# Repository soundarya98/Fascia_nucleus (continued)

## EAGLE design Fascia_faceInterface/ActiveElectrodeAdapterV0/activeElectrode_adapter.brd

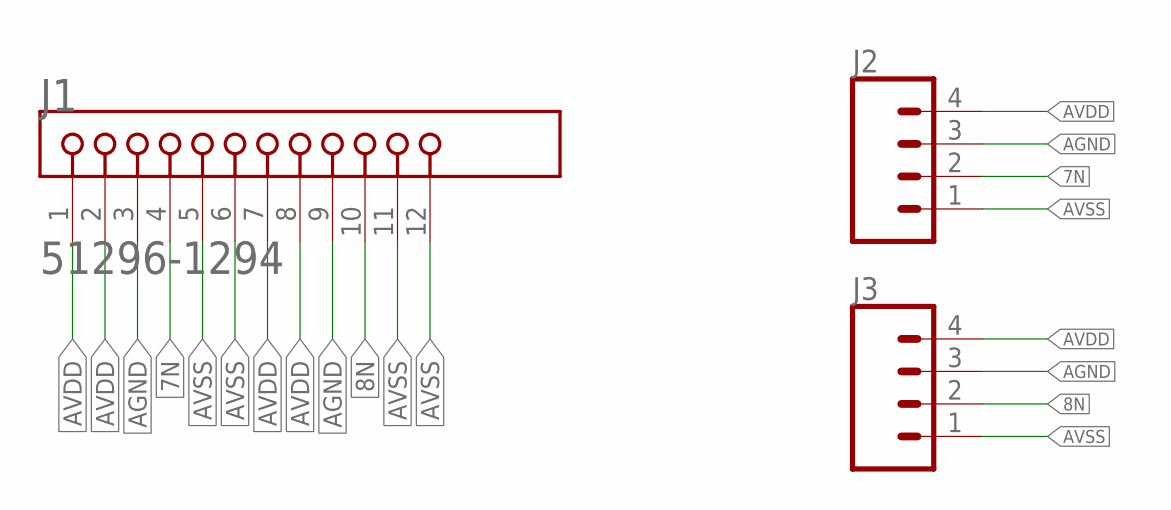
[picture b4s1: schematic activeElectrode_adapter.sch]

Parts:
J1: MOLEX_51296-1294_FLEX
J2, J3: CONN_04AE_4PIN; AE-4-PTH

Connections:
7N: J1.4, J2.2
8N: J1.10, J3.2
AGND: J1.3, J1.9, J2.3, J3.3
AVDD: J1.1, J1.2, J1.7, J1.8, J2.4, J3.4
AVSS: J1.5, J1.6, J1.11, J1.12, J2.1, J3.1

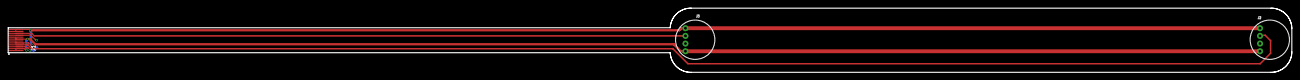
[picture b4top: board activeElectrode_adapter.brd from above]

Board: 2 copper layers, 334.2 x 16.7 mm, 3 parts (0 on the bottom side), 5 nets.

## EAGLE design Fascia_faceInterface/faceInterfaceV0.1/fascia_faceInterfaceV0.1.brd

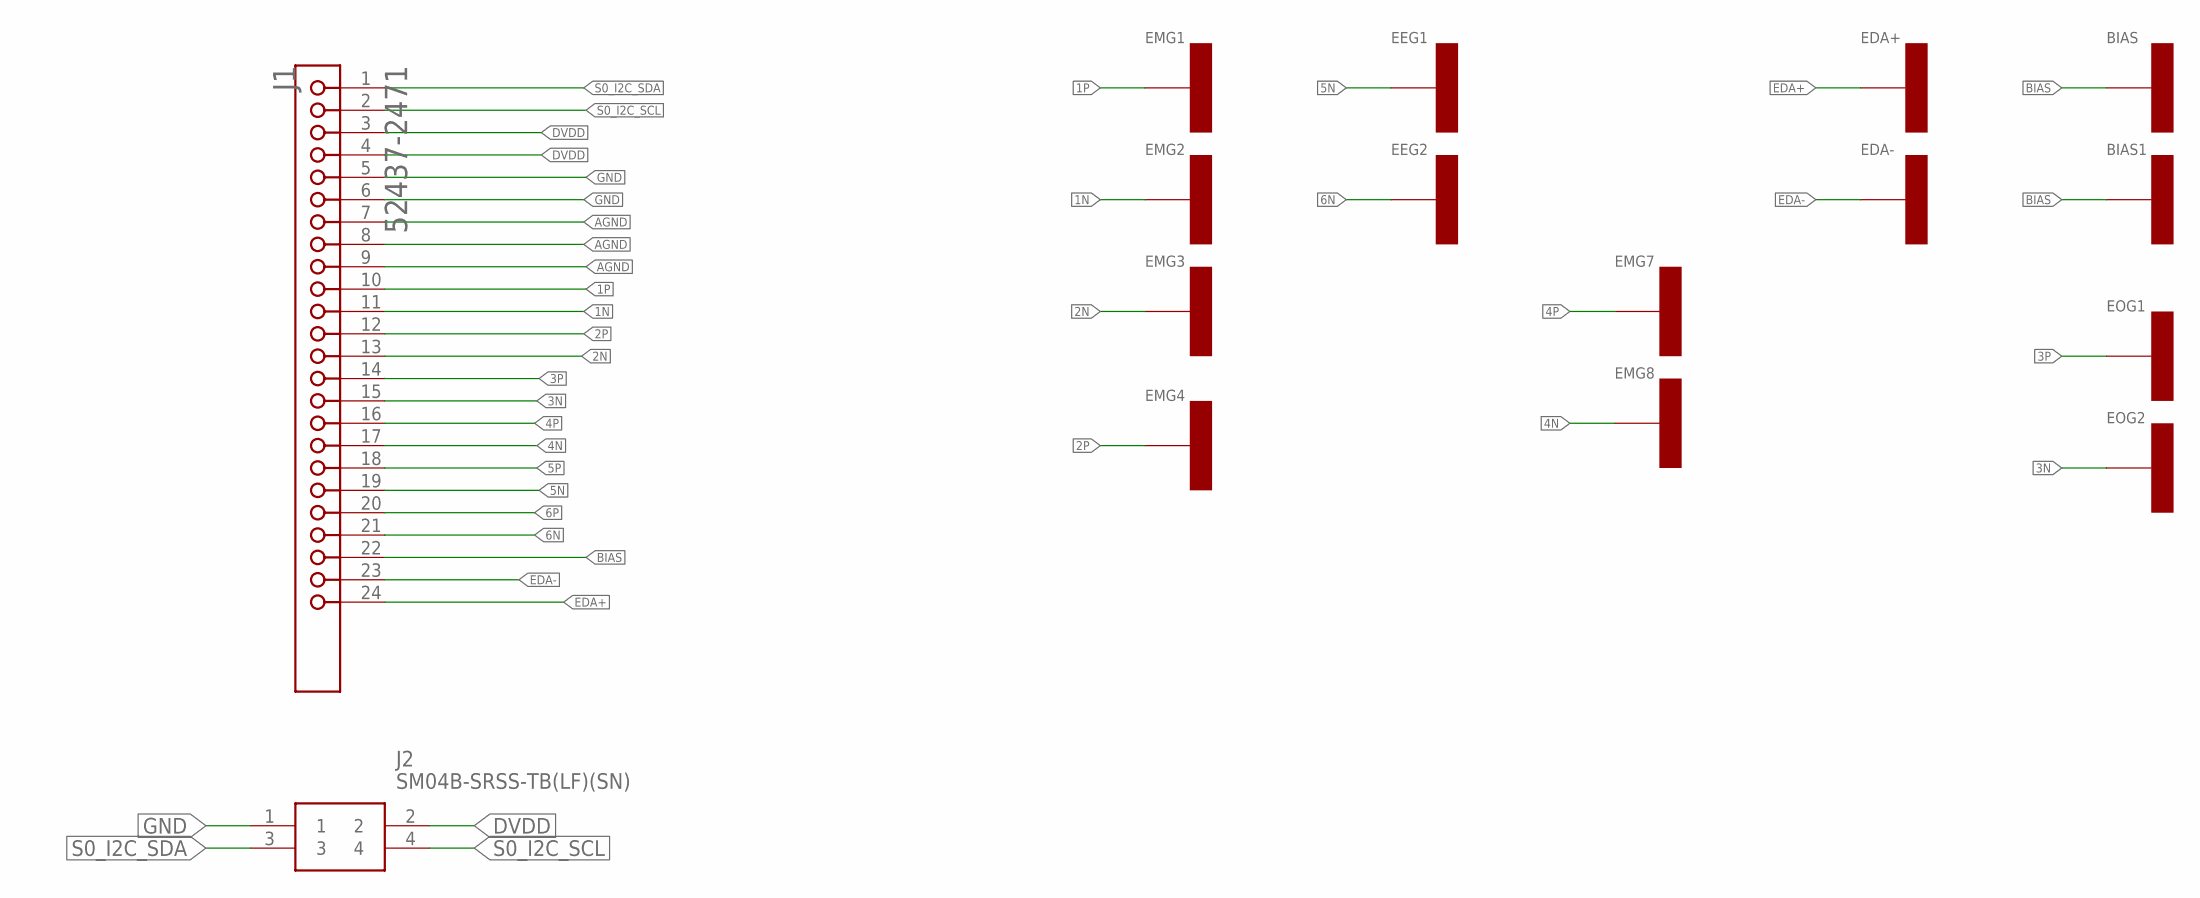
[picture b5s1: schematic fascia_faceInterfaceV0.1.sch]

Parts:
BIAS, BIAS1: ELECTRODE-8MMELECTRODE_8MM; ELECTRODE_V2
EDA+: ELECTRODE-8MMELECTRODE_8MM; ELECTRODE_V2
EDA-: ELECTRODE-8MMELECTRODE_8MM; ELECTRODE_V2
EEG1, EEG2: ELECTRODE-8MMELECTRODE_8MM; ELECTRODE_V2
EMG1, EMG2, EMG3, EMG4, EMG7, EMG8: ELECTRODE-8MMELECTRODE_8MM; ELECTRODE_V2
EOG1, EOG2: ELECTRODE-8MMELECTRODE_8MM; ELECTRODE_V2
J1: MOLEX_52437-247_FLEX; MOLEX_52437-2471_FLEX
J2: SM04B-SRSS-TB(LF)(SN); SM04B-SRSS-TB(LFSN)

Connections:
1N: EMG2.,, EMG2.., EMG2.P$1, EMG2.P$2, EMG2.P$3, EMG2.P$4, J1.11
1P: EMG1.,, EMG1.., EMG1.P$1, EMG1.P$2, EMG1.P$3, EMG1.P$4, J1.10
2N: EMG3.,, EMG3.., EMG3.P$1, EMG3.P$2, EMG3.P$3, EMG3.P$4, J1.13
2P: EMG4.,, EMG4.., EMG4.P$1, EMG4.P$2, EMG4.P$3, EMG4.P$4, J1.12
3N: EOG2.,, EOG2.., EOG2.P$1, EOG2.P$2, EOG2.P$3, EOG2.P$4, J1.15
3P: EOG1.,, EOG1.., EOG1.P$1, EOG1.P$2, EOG1.P$3, EOG1.P$4, J1.14
4N: EMG8.,, EMG8.., EMG8.P$1, EMG8.P$2, EMG8.P$3, EMG8.P$4, J1.17
4P: EMG7.,, EMG7.., EMG7.P$1, EMG7.P$2, EMG7.P$3, EMG7.P$4, J1.16
5N: EEG1.,, EEG1.., EEG1.P$1, EEG1.P$2, EEG1.P$3, EEG1.P$4, J1.19
5P: J1.18
6N: EEG2.,, EEG2.., EEG2.P$1, EEG2.P$2, EEG2.P$3, EEG2.P$4, J1.21
6P: J1.20
AGND: J1.7, J1.8, J1.9
BIAS: BIAS.,, BIAS.., BIAS.P$1, BIAS.P$2, BIAS.P$3, BIAS.P$4, BIAS1.,, BIAS1.., BIAS1.P$1, BIAS1.P$2, BIAS1.P$3, BIAS1.P$4, J1.22
DVDD: J1.3, J1.4, J2.2
EDA+: EDA+.,, EDA+.., EDA+.P$1, EDA+.P$2, EDA+.P$3, EDA+.P$4, J1.24
EDA-: EDA-.,, EDA-.., EDA-.P$1, EDA-.P$2, EDA-.P$3, EDA-.P$4, J1.23
GND: J1.5, J1.6, J2.1
S0_I2C_SCL: J1.2, J2.4
S0_I2C_SDA: J1.1, J2.3

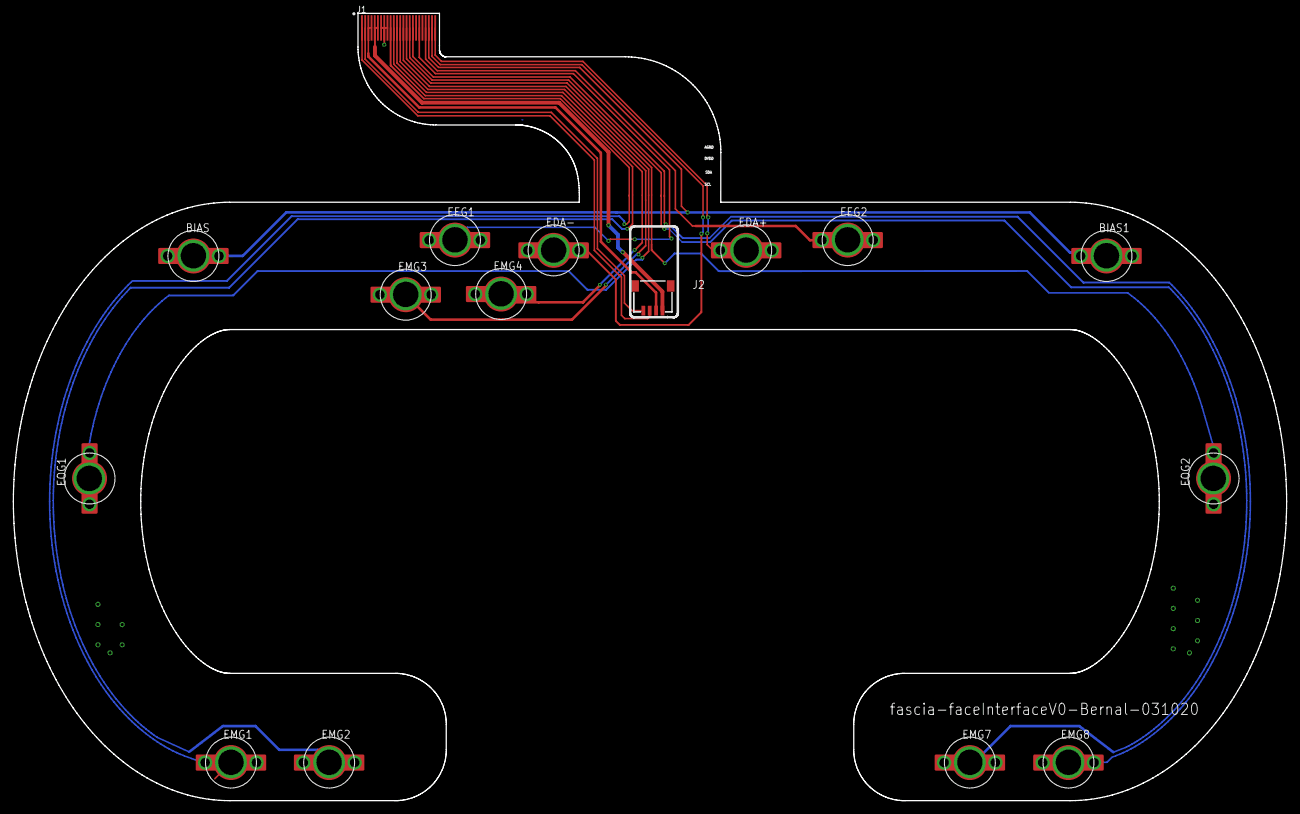
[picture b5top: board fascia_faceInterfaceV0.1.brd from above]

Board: 2 copper layers, 200.0 x 123.7 mm, 16 parts (0 on the bottom side), 18 nets.

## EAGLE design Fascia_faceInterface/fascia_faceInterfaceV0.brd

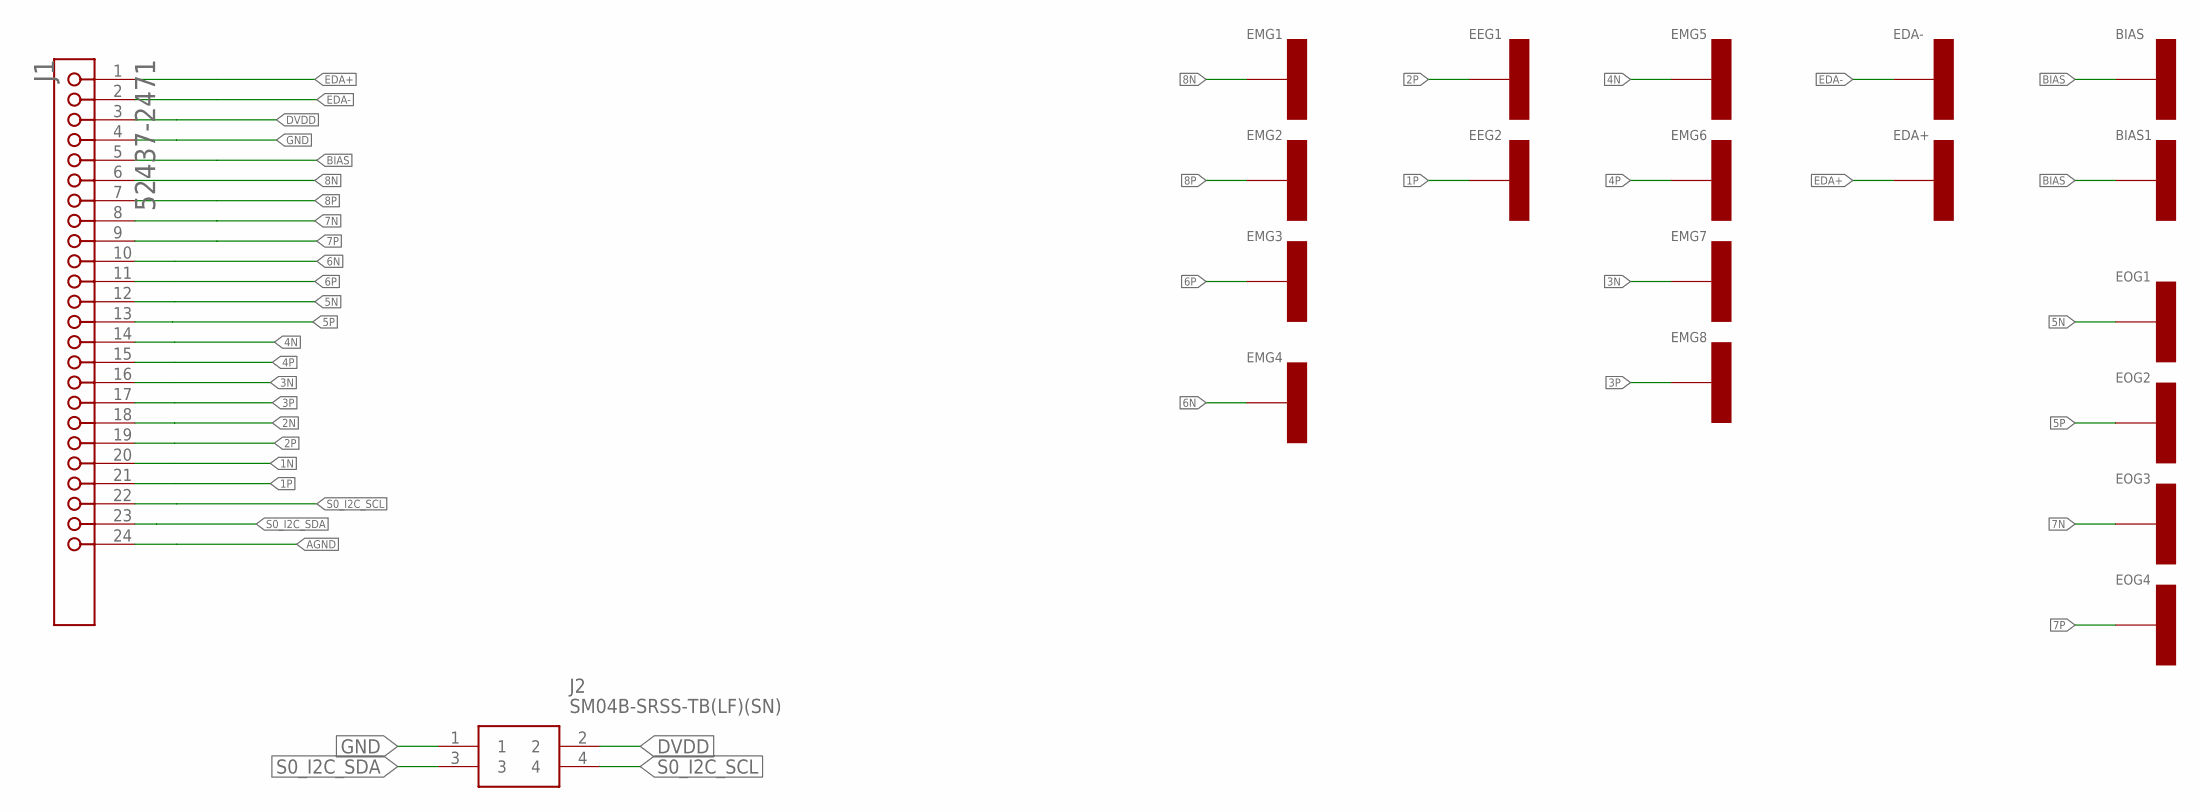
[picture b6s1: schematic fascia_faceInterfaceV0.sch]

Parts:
BIAS, BIAS1: ELECTRODE-8MMELECTRODE_8MM; ELECTRODE_V2
EDA+: ELECTRODE-8MMELECTRODE_8MM; ELECTRODE_V2
EDA-: ELECTRODE-8MMELECTRODE_8MM; ELECTRODE_V2
EEG1, EEG2: ELECTRODE-8MMELECTRODE_8MM; ELECTRODE_V2
EMG1, EMG2, EMG3, EMG4, EMG5, EMG6, EMG7, EMG8: ELECTRODE-8MMELECTRODE_8MM; ELECTRODE_V2
EOG1, EOG2, EOG3, EOG4: ELECTRODE-8MMELECTRODE_8MM; ELECTRODE_V2
J1: MOLEX_52437-247_FLEX; MOLEX_52437-2471_FLEX
J2: SM04B-SRSS-TB(LF)(SN); SM04B-SRSS-TB(LFSN)

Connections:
1N: J1.20
1P: EEG2.,, EEG2.., EEG2.P$1, EEG2.P$2, EEG2.P$3, EEG2.P$4, J1.21
2N: J1.18
2P: EEG1.,, EEG1.., EEG1.P$1, EEG1.P$2, EEG1.P$3, EEG1.P$4, J1.19
3N: EMG7.,, EMG7.., EMG7.P$1, EMG7.P$2, EMG7.P$3, EMG7.P$4, J1.16
3P: EMG8.,, EMG8.., EMG8.P$1, EMG8.P$2, EMG8.P$3, EMG8.P$4, J1.17
4N: EMG5.,, EMG5.., EMG5.P$1, EMG5.P$2, EMG5.P$3, EMG5.P$4, J1.14
4P: EMG6.,, EMG6.., EMG6.P$1, EMG6.P$2, EMG6.P$3, EMG6.P$4, J1.15
5N: EOG1.,, EOG1.., EOG1.P$1, EOG1.P$2, EOG1.P$3, EOG1.P$4, J1.12
5P: EOG2.,, EOG2.., EOG2.P$1, EOG2.P$2, EOG2.P$3, EOG2.P$4, J1.13
6N: EMG4.,, EMG4.., EMG4.P$1, EMG4.P$2, EMG4.P$3, EMG4.P$4, J1.10
6P: EMG3.,, EMG3.., EMG3.P$1, EMG3.P$2, EMG3.P$3, EMG3.P$4, J1.11
7N: EOG3.,, EOG3.., EOG3.P$1, EOG3.P$2, EOG3.P$3, EOG3.P$4, J1.8
7P: EOG4.,, EOG4.., EOG4.P$1, EOG4.P$2, EOG4.P$3, EOG4.P$4, J1.9
8N: EMG1.,, EMG1.., EMG1.P$1, EMG1.P$2, EMG1.P$3, EMG1.P$4, J1.6
8P: EMG2.,, EMG2.., EMG2.P$1, EMG2.P$2, EMG2.P$3, EMG2.P$4, J1.7
AGND: J1.24
BIAS: BIAS.,, BIAS.., BIAS.P$1, BIAS.P$2, BIAS.P$3, BIAS.P$4, BIAS1.,, BIAS1.., BIAS1.P$1, BIAS1.P$2, BIAS1.P$3, BIAS1.P$4, J1.5
DVDD: J1.3, J2.2
EDA+: EDA+.,, EDA+.., EDA+.P$1, EDA+.P$2, EDA+.P$3, EDA+.P$4, J1.1
EDA-: EDA-.,, EDA-.., EDA-.P$1, EDA-.P$2, EDA-.P$3, EDA-.P$4, J1.2
GND: J1.4, J2.1
S0_I2C_SCL: J1.22, J2.4
S0_I2C_SDA: J1.23, J2.3

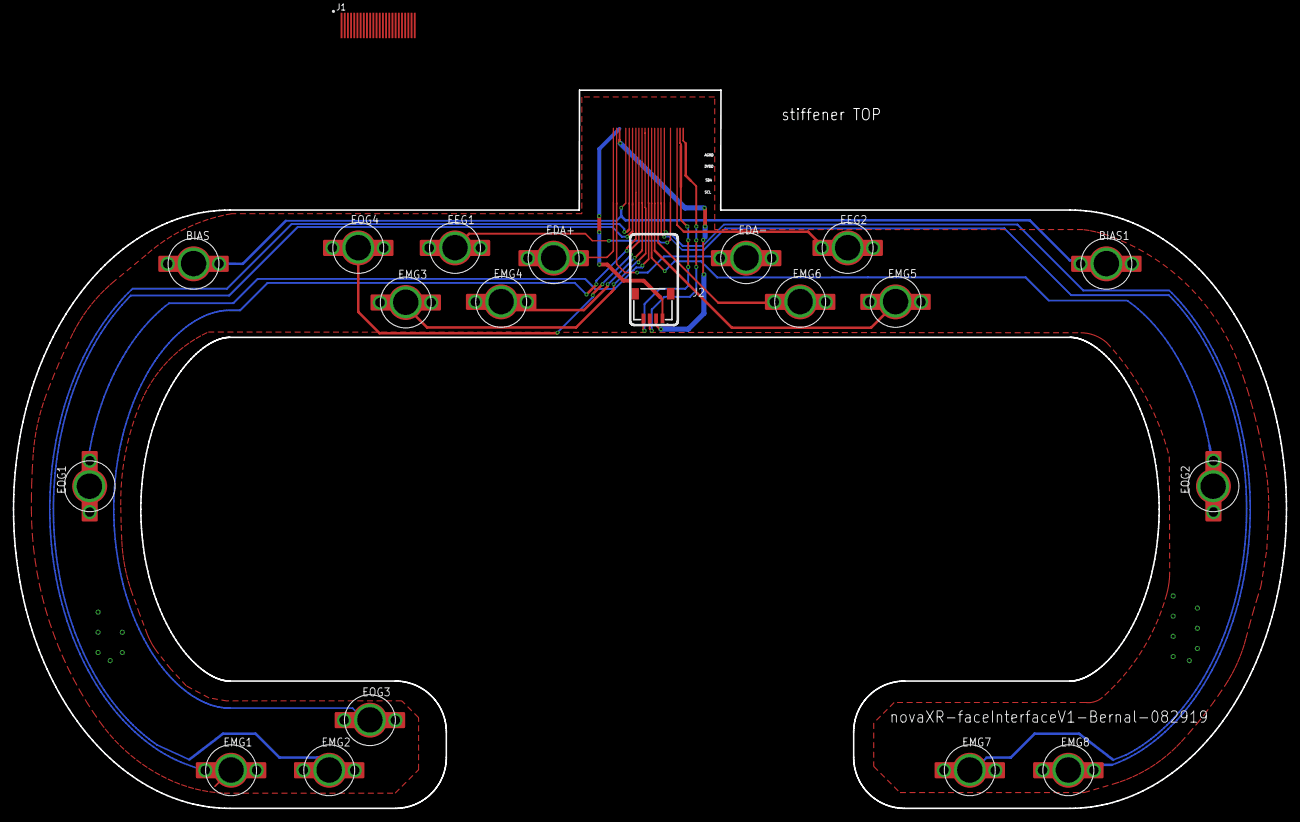
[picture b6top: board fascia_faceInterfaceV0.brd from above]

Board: 2 copper layers, 200.0 x 112.8 mm, 20 parts (0 on the bottom side), 21 nets.

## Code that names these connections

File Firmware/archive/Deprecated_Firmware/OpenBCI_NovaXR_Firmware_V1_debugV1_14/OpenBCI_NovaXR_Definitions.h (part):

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// ----------------------//----------------------//-------------//

// ###################### SAMD21 Pin Table ####################
#define PA02 15 // =========== NXR2: A0 - EDA Signal
#define PA05 19 // =========== NXR2: A4 - VBATT Level
#define PA06 20 // =========== NXR2: A5 - DVDD_ISO - EDA circuit VDD
#define PB09 32 // =========== NXR2: A2 - DGND_ISO - EDA Circuite GND


#define PB02 16 // =========== NXR2: A1 - HW EXT interrupt DRDY 2
#define PB10 4  // =========== NXR2: D4 - HW EXT interrupt DRDY 1
#define PA20 6  // =========== NXR2: ADS1299 #1 - SPI CS2
#define PA21 7  // =========== NXR2: ADS1299 #0 - SPI CS1


#define PA07 21 // =========== NXR1: A6 - ADS1299 #1 - DRDY Sister Board
#define PA10 2  // =========== NXR1: ADS1299 #0 - DRDY
#define PA04 18 // =========== NXR1: LED Red
#define PA18 24 // =========== NXR1: USB OTG sense

#define PA16 8  // =========== NXR1: ADS1299 #0/#1 - SPI MOSI
#define PA17 9  // =========== NXR1: ADS1299 #0/#1 - SPI SCK
#define PA19 10 // =========== NXR1: ADS1299 #0/#1 - SPI MISO


#define PB08 31 // =========== NXR1: uBlox RST
#define PA08 11 // =========== NXR1: uBlox & IMU & Crypto - I2C 
#define PA09 12 // =========== NXR1: uBlox & IMU & Crypto - I2C 
#define PA12 26 // =========== NXR1: uBlox - TX_MOSI
#define PA13 27 // =========== NXR1: uBlox - RX_MISO
#define PA14 28 // =========== NXR1: uBlox - RTS_CS
#define PA15 29 // =========== NXR1: uBlox - CTS_SCK
#define PA27 30 // =========== NXR1: uBlox - GPIO0
#define PA28 35 // =========== NXR1: uBlox - ACK
#define PB22 14 // =========== NXR1: uBlox - TX
#define PB23 13 // =========== NXR1: uBlox - RX

#define PA11 3 
#define PB11 5   
#define PA22 0
#define PA23 1 
#define PB02 16 
#define PB03 17 
#define PA03 25 


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//**********************//**********************//**********************//**********************
#define CH_NORMAL_ELECTRODE     0           ///< Channel is connected to the corresponding positive and negative input pins.
#define CH_INPUT_SHORTED        1           ///< Channel inputs are shorted together. Used for offset and noise measurements.
#define CH_BIAS_MEASUREMENT     2           ///< Used with CONFIG3.BIAS_MEAS for bias measurement. See ADS1299 datasheet, pp. 53-54.
#define CH_MVDD_SUPPLY          3           ///< Used for measuring analog and digital supplies. See ADS1299 datasheet, p. 17.
#define CH_TEMPERATURE_SENSOR   4           ///< Measures device temperature. See ADS1299 datasheet, p. 17.
#define CH_TEST_SIGNAL          5           ///< Measures calibration signal. See ADS1299 datasheet, pp. 17 and 41.
#define CH_BIAS_DRIVE_P         6           ///< Connects positive side of channel to bias drive output.
#define CH_BIAS_DRIVE_N         7           ///< Connects negative side of channel to bias drive output.
#define CHANNEL_ON             (0<<7)
#define CHANNEL_OFF            (1<<7)
#define CH_SRB2_DISCONNECTED   (0<<3)
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
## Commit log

2019-11-15 initial changes
2019-11-15 added files for the physioBoard
2019-11-15 initital changes to physioBoard
2019-11-15 minor updates
2019-11-15 minor changes
2019-11-18 minor layout changes
2019-11-18 wiring progress
2019-11-20 finished routing physio board, bunch of warnings in ERC and a few width errors in DRC
2019-11-20 added one route that was missing in the previous commit
2019-11-20 fixed some traces and completed board traces
2019-11-21 minor change
2019-11-21 added firmware folder
2019-11-21 progress on routing
2019-11-22 maiboard routing completed
2019-11-22 files ready for manufacture
2020-01-07 first update to project in year 2020
2020-01-29 changes to the power supply and holder for the pcb
2020-02-02 changes for making firmaware to work with novaxr main v2
2020-02-03 added reference files
2020-02-03 reference to the physiohmd library
2020-02-07 added development folder with most recent firmware for novaxr
2020-02-17 changes to the fascia boards
2020-02-20 adding new single shot mode to master Fascia repo. It is its own git repo locally but will not be embedding here for simplicity
2020-02-20 minor chabges to physio board
2020-02-21 firmware dev: SingleShot: removed delay in main loop, and fixed reading two registers when trying to read one
2020-02-21 dev firmware: added working continuous conversion code
2020-02-22 Walaas cnages for wifi
2020-02-22 Walas work
2020-02-24 working change of per channel gain thru serial and SRB2
2020-02-24 cleanup and make sure gain works for both ss and cc
2020-02-26 fixed continuous conversion, which I broke a couple of commits ago
2020-02-26 added serial functionality to turn on and off channel
2020-02-26 some cleanup
2020-02-28 changed file name for testing code
2020-02-28 removed .vscode dir
2020-02-28 merging and adding single shot mode alone
2020-02-28 clean up
2020-02-28 added more readable binary codes
2020-02-28 more clean up, compiling now because removed accidental half written code
2020-03-03 firmware: added serial enable/disable bias and SRB2
2020-03-03 Fixed SRB2 SRB1 issue
2020-03-04 fixed issues related to missing traces from pin 1 to the feedback to pin 2
2020-03-05 removed wrong component
2020-03-05 changes to issue with R13
2020-03-06 added Seans optoisolator circuit
2020-03-06 initial fascia collect sensor data
2020-03-06 Modifications to serial interface
2020-03-08 made changes to eda schematic and board files. fixing the issues preventing the V0 to work correctly
2020-03-10 some progress for the new face interface
2020-03-10 flexible boards files submitted for fabrication
2020-03-11 update to board files for manufacturing
2020-03-13 cleanup and working streaming of all sensor data
2020-03-13 changed number of IMU channels to 6
2020-03-13 adding data visualization python programs
2020-03-13 adding libraries for arduino firmware in firmware/development/libraries
2020-03-17 fixing faceinterface
2020-03-17 Fixes for the faceinterface issue
2020-03-19 quick updates
2020-03-19 lower sample rate for PPG sensor- it is slow, and modified the library to be faster
2020-03-19 dataviz changes to match the firmware changes- added battery plot and data rate calculation
2020-03-19 sampling rate improved- sampling PPG/TEMP sensor once every 10 packets. removed battery data. adjsuted python data viz accordingly
2020-03-19 adding modified library
2020-03-19 hose keeping
2020-03-23 improved data rate by a lotgit status Sped up analogRead() by a lot, and increased analogRead for EDA resolution from 10 to 12 bits
2020-03-25 added ADS viz code and implemented FFT and graphing it- freq units not Hz yet
2020-03-25 implemented a thread to calculate the FFT- because it was slow and interfering with data rate. DR still is slower due to calculation, but i think we have Hz already
2020-03-27 added semi functional heart rate algorithm, and added text to GUI for heart rate, packet#, and data rate. GUI window freezes/jams sometimes and resizing seems to refresh it and get it working again
2020-03-30 added EDA Rskin calc function- untested but based on the circuit and values
2020-03-31 int -> float typo in Vref
2020-03-31 adding EDA testing code
2020-03-31 added biasN and biasP distinction for functions to change channel settings using serial communication
2020-04-06 improved heartrate alogirthm
2020-04-06 adding .pyc files to ignore
2020-04-06 made changes for FFT code, and profiling the code- speed improved too
2020-04-07 added more pyc files
2020-04-07 made improvements to heart rate algorithm, and implemented optionally skipping the first n graphs in the GUI
2020-04-08 implemented averaging and converting EDA data from ADC counts to Rskin
2020-04-10 incorporated FFT to fascia code, and did some clean up
2020-04-10 removed outdated files
2020-04-10 fixed some bugs w/ integrating optional FFT plotting
2020-04-14 incorporated real IMU code/ data collection. Make sure to comment out/in the sensor data for sensors you dont/do have (respectively)
2020-04-14 modified firmware to convert ADS data to volts before sending to dataViz, also fixed graph labels in datA VIZ
2020-04-14 applying the appropriate filters to each ADS channel
2020-04-22 changed values used on the board to be reflected on the schematic
2020-04-28 added print all register contents of ADS1299 functionality
2020-04-28 updated values for EDA v1
2020-05-11 some clean up
2020-05-15 added commented out code to perform conversion for IMU data (more changes required than just uncommenting in order to get the data sent over)
2020-05-15 fixed an issue with ADS1299 serial debug interface with biasN and biasP
2020-05-15 array size issue for the same biasP/N issue
2020-05-30 changes to make Fascia profilable and to show accurate Arduino data rate on GUI
2020-08-18 deepsleepnet replication
2020-08-25 Naive LSTM
2020-08-31 Added comparison of various state of the arts
2020-08-31 Added summary files
2020-09-07 PSG halfway done. Added support for PSG, halfway
2020-09-08 Enabled PSG Log voting
2020-09-08 Refactored code to different directories
2020-09-08 Added files after refactoring into different directories
2020-09-08 Fixed prediction errors
2020-09-10 AWS setup + PSG logits for single 30s epoch completed
2020-09-14 DeepSleepNet keras
2020-09-22 With speech models
2020-10-07 Post visualizations
2020-10-08 adding files for local upload and web interface
2020-12-02 With gradcam and explanations
